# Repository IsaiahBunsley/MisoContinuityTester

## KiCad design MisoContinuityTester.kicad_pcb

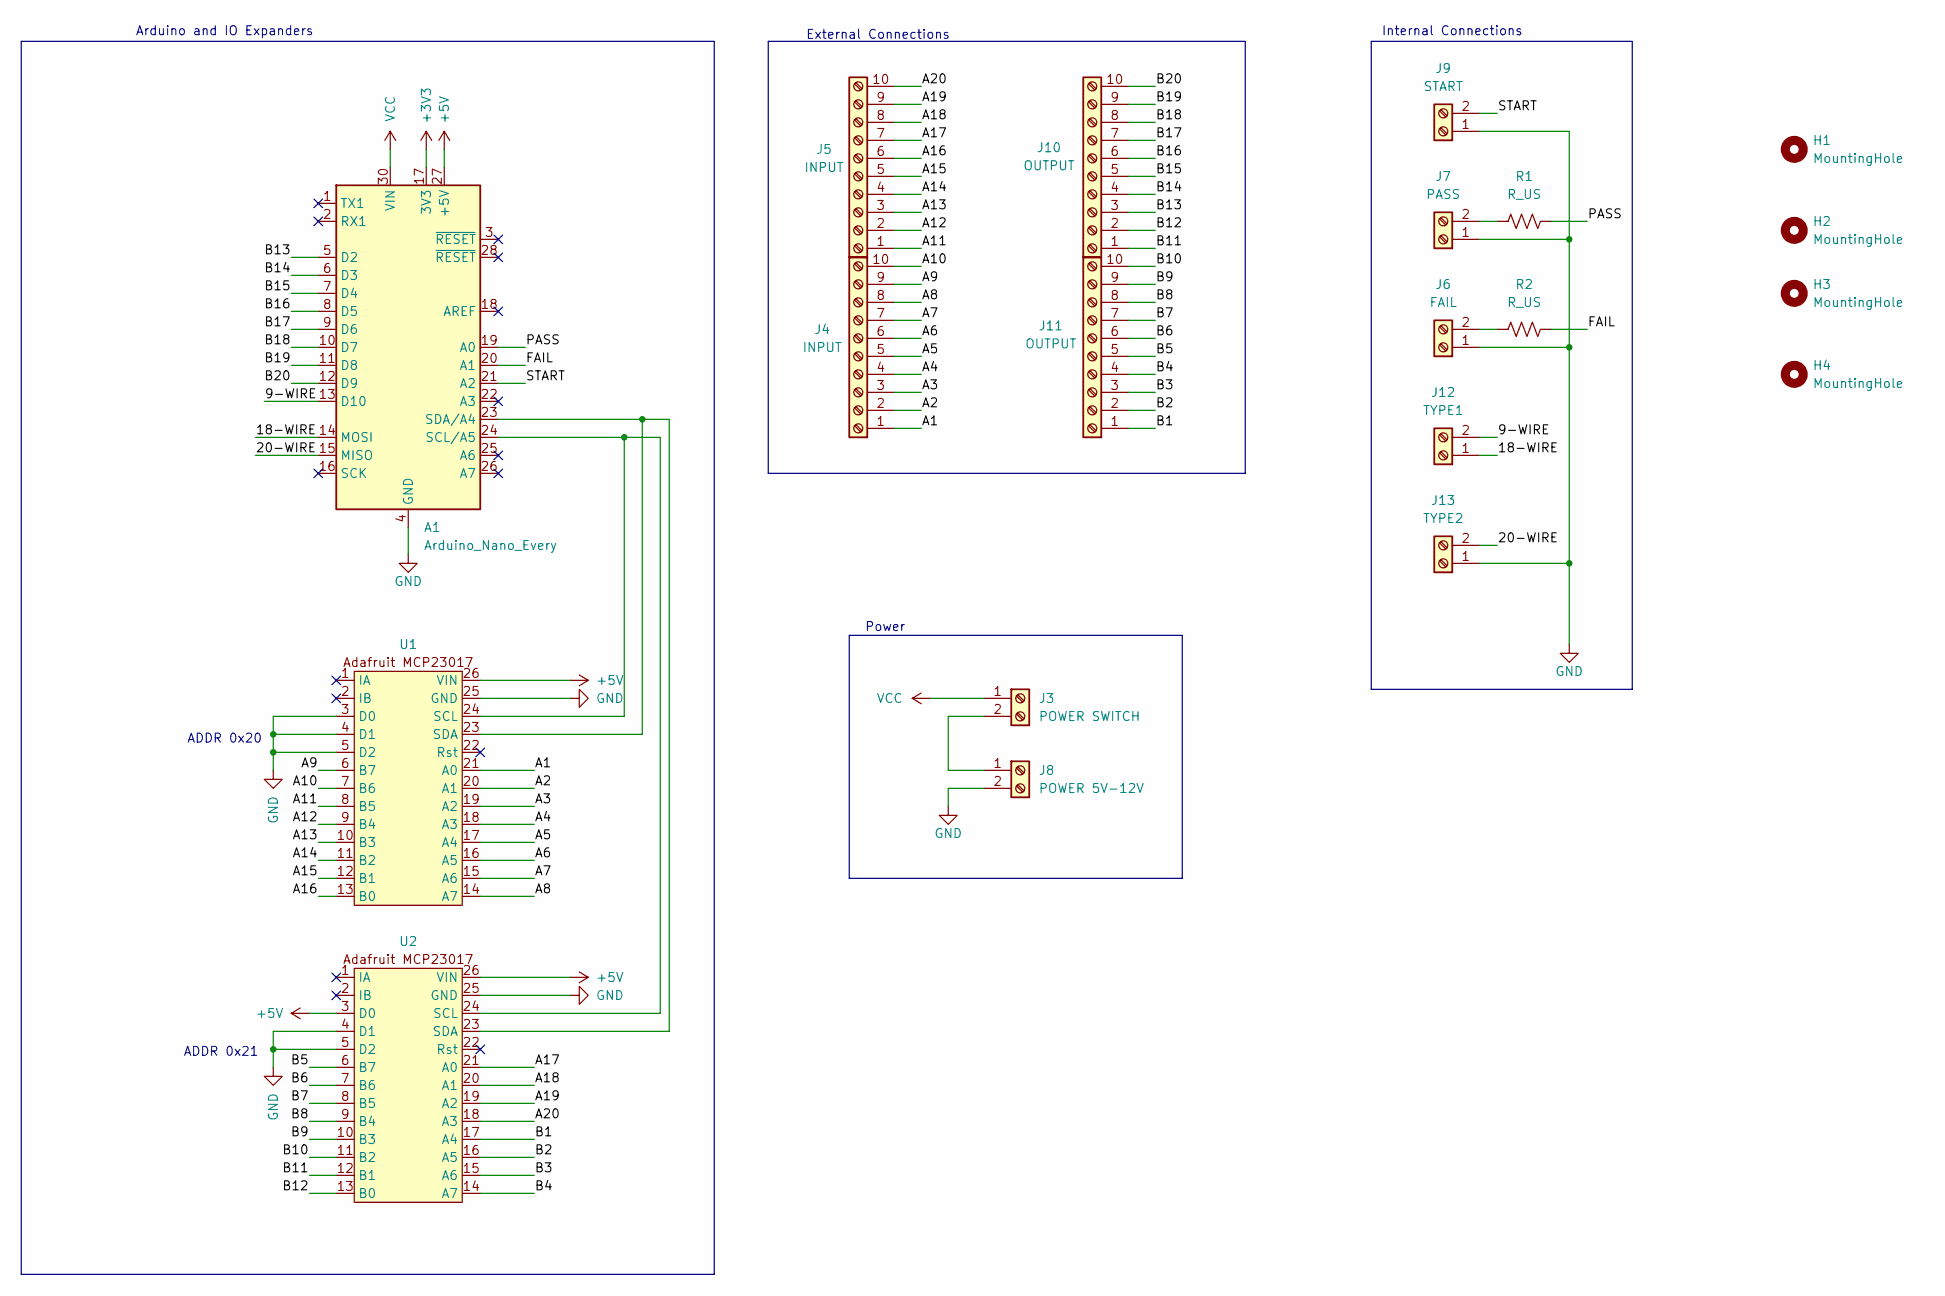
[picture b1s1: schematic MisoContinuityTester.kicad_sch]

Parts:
A1: Arduino_Nano_Every; Arduino_Nano
H1, H2, H3, H4: MountingHole; MountingHole_4.3mm_M4
J3: POWER SWITCH; TerminalBlock_Phoenix_MPT-0,5-2-2.54_1x02_P2.54mm_Horizontal
J4, J5: INPUT; TerminalBlock_Xinya_XY308-2.54-10P_1x10_P2.54mm_Horizontal
J6: FAIL; TerminalBlock_Phoenix_MPT-0,5-2-2.54_1x02_P2.54mm_Horizontal
J7: PASS; TerminalBlock_Phoenix_MPT-0,5-2-2.54_1x02_P2.54mm_Horizontal
J8: POWER 5V-12V; TerminalBlock_Phoenix_MPT-0,5-2-2.54_1x02_P2.54mm_Horizontal
J9: START; TerminalBlock_Phoenix_MPT-0,5-2-2.54_1x02_P2.54mm_Horizontal
J10, J11: OUTPUT; TerminalBlock_Xinya_XY308-2.54-10P_1x10_P2.54mm_Horizontal
J12: TYPE1; TerminalBlock_Phoenix_MPT-0,5-2-2.54_1x02_P2.54mm_Horizontal
J13: TYPE2; TerminalBlock_Phoenix_MPT-0,5-2-2.54_1x02_P2.54mm_Horizontal
R1, R2: R_US; R_Axial_DIN0204_L3.6mm_D1.6mm_P5.08mm_Horizontal
U1, U2: Adafruit MCP23017

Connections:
+3V3: A1.17 (3V3)
+5V: A1.27 (+5V), U1.26 (VIN), U2.3 (D0), U2.26 (VIN)
/9-WIRE: A1.13 (D10), J12.2
/18-WIRE: A1.14 (MOSI), J12.1
/20-WIRE: A1.15 (MISO), J13.2
/A1: J4.1, U1.21 (A0)
/A2: J4.2, U1.20 (A1)
/A3: J4.3, U1.19 (A2)
/A4: J4.4, U1.18 (A3)
/A5: J4.5, U1.17 (A4)
/A6: J4.6, U1.16 (A5)
/A7: J4.7, U1.15 (A6)
/A8: J4.8, U1.14 (A7)
/A9: J4.9, U1.6 (B7)
/A10: J4.10, U1.7 (B6)
/A11: J5.1, U1.8 (B5)
/A12: J5.2, U1.9 (B4)
/A13: J5.3, U1.10 (B3)
/A14: J5.4, U1.11 (B2)
/A15: J5.5, U1.12 (B1)
/A16: J5.6, U1.13 (B0)
/A17: J5.7, U2.21 (A0)
/A18: J5.8, U2.20 (A1)
/A19: J5.9, U2.19 (A2)
/A20: J5.10, U2.18 (A3)
/B1: J11.1, U2.17 (A4)
/B2: J11.2, U2.16 (A5)
/B3: J11.3, U2.15 (A6)
/B4: J11.4, U2.14 (A7)
/B5: J11.5, U2.6 (B7)
/B6: J11.6, U2.7 (B6)
/B7: J11.7, U2.8 (B5)
/B8: J11.8, U2.9 (B4)
/B9: J11.9, U2.10 (B3)
/B10: J11.10, U2.11 (B2)
/B11: J10.1, U2.12 (B1)
/B12: J10.2, U2.13 (B0)
/B13: A1.5 (D2), J10.3
/B14: A1.6 (D3), J10.4
/B15: A1.7 (D4), J10.5
/B16: A1.8 (D5), J10.6
/B17: A1.9 (D6), J10.7
/B18: A1.10 (D7), J10.8
/B19: A1.11 (D8), J10.9
/B20: A1.12 (D9), J10.10
/FAIL: A1.20 (A1), R2.2
/PASS: A1.19 (A0), R1.2
/START: A1.21 (A2), J9.2
GND: A1.4 (GND), A1.29 (GND), J6.1, J7.1, J8.2, J9.1, J13.1, U1.3 (D0), U1.4 (D1), U1.5 (D2), U1.25 (GND), U2.4 (D1), U2.5 (D2), U2.25 (GND)
unnamed: A1.24 (SCL/A5), U1.24 (SCL), U2.24 (SCL)
unnamed: A1.23 (SDA/A4), U1.23 (SDA), U2.23 (SDA)
unnamed: J3.2, J8.1
unnamed: J6.2, R2.1
unnamed: J7.2, R1.1
VCC: A1.30 (VIN), J3.1

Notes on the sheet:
ADDR 0x21
Power
ADDR 0x20
External Connections
Arduino and IO Expanders
Internal Connections

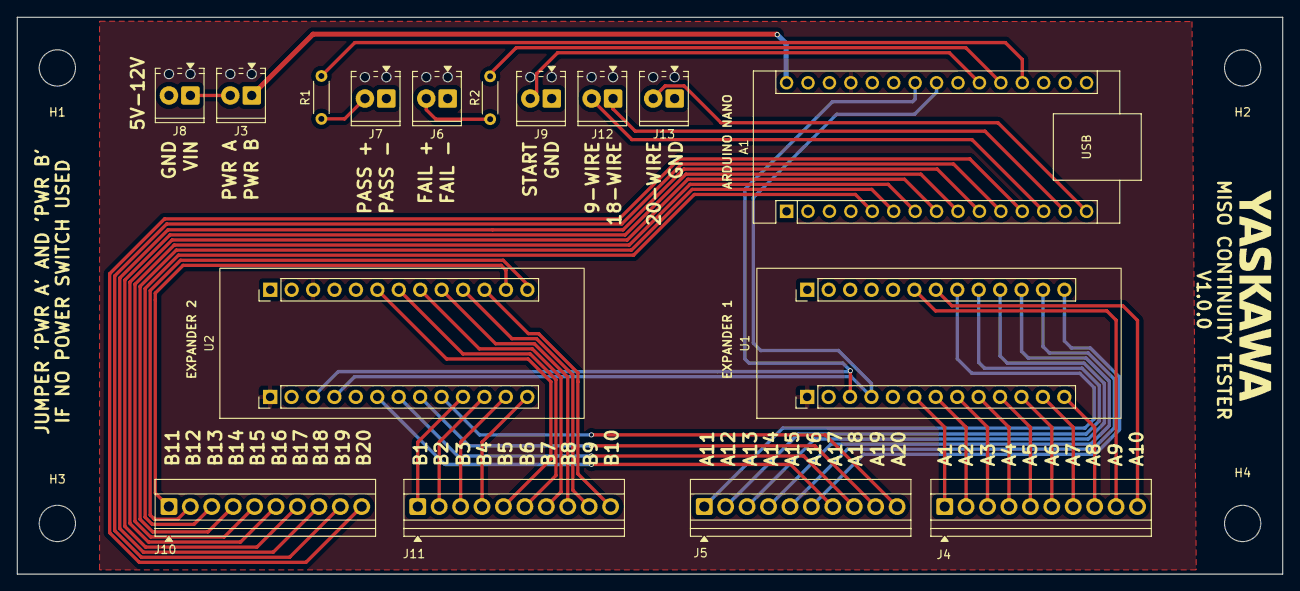
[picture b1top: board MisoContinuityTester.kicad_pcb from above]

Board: 2 copper layers, 150.0 x 66.0 mm, 20 parts (0 on the bottom side), 54 nets.

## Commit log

2025-05-15 initial
2025-05-15 added 3d models, worked on pcb
2025-05-16 added mounting holes
2025-05-16 wired everything up and added resistors for pass and fail
2025-05-19 See OneDrive notes - IB
2025-05-19 added lables
2025-05-19 Added 'start' button labels
2025-05-19 added lables Expander 1 and Expander 2 so we can tell each expanders i/o pins a part
2025-05-30 connected adress pins from Exp 1 and 2 to NANO, changed around where the switchs all go
2025-06-02 re fix the mounting holes.
